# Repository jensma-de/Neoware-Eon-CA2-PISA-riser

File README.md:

# Neoware Eon/CA2 PISA to ISA/PCI Riser Card

An exact 1:1 reproduction of the original riser card used in Neoware Eon/CA2 systems. This riser card enables the conversion of PISA to ISA and PCI.

[./production.zip](./production.zip) contains gerber files and everything needed to manufacture this card.

## Features

- **Function**: Converts PISA to ISA & PCI
- **Voltage Converter**: I added an integrated -5V voltage converter for the ISA slot
- **Condition**: New, 1:1 reproduction of the original card (except for the -5V voltage converter)
- **Compatibility**: Identical to the card installed in Neoware Eon/CA2

# Schematics

I annotated the schematics to clarify some quirks:

## License

This project is licensed under the MIT License. See the [LICENSE](LICENSE) file for more details.

## Thanks

I extend my sincere gratitude to (https://www.parkytowers.me.uk/) for the generous loan of an original Neoware CA2 riser card. Your support was instrumental in enabling the accurate reproduction of this hardware. Thank you for your invaluable assistance.

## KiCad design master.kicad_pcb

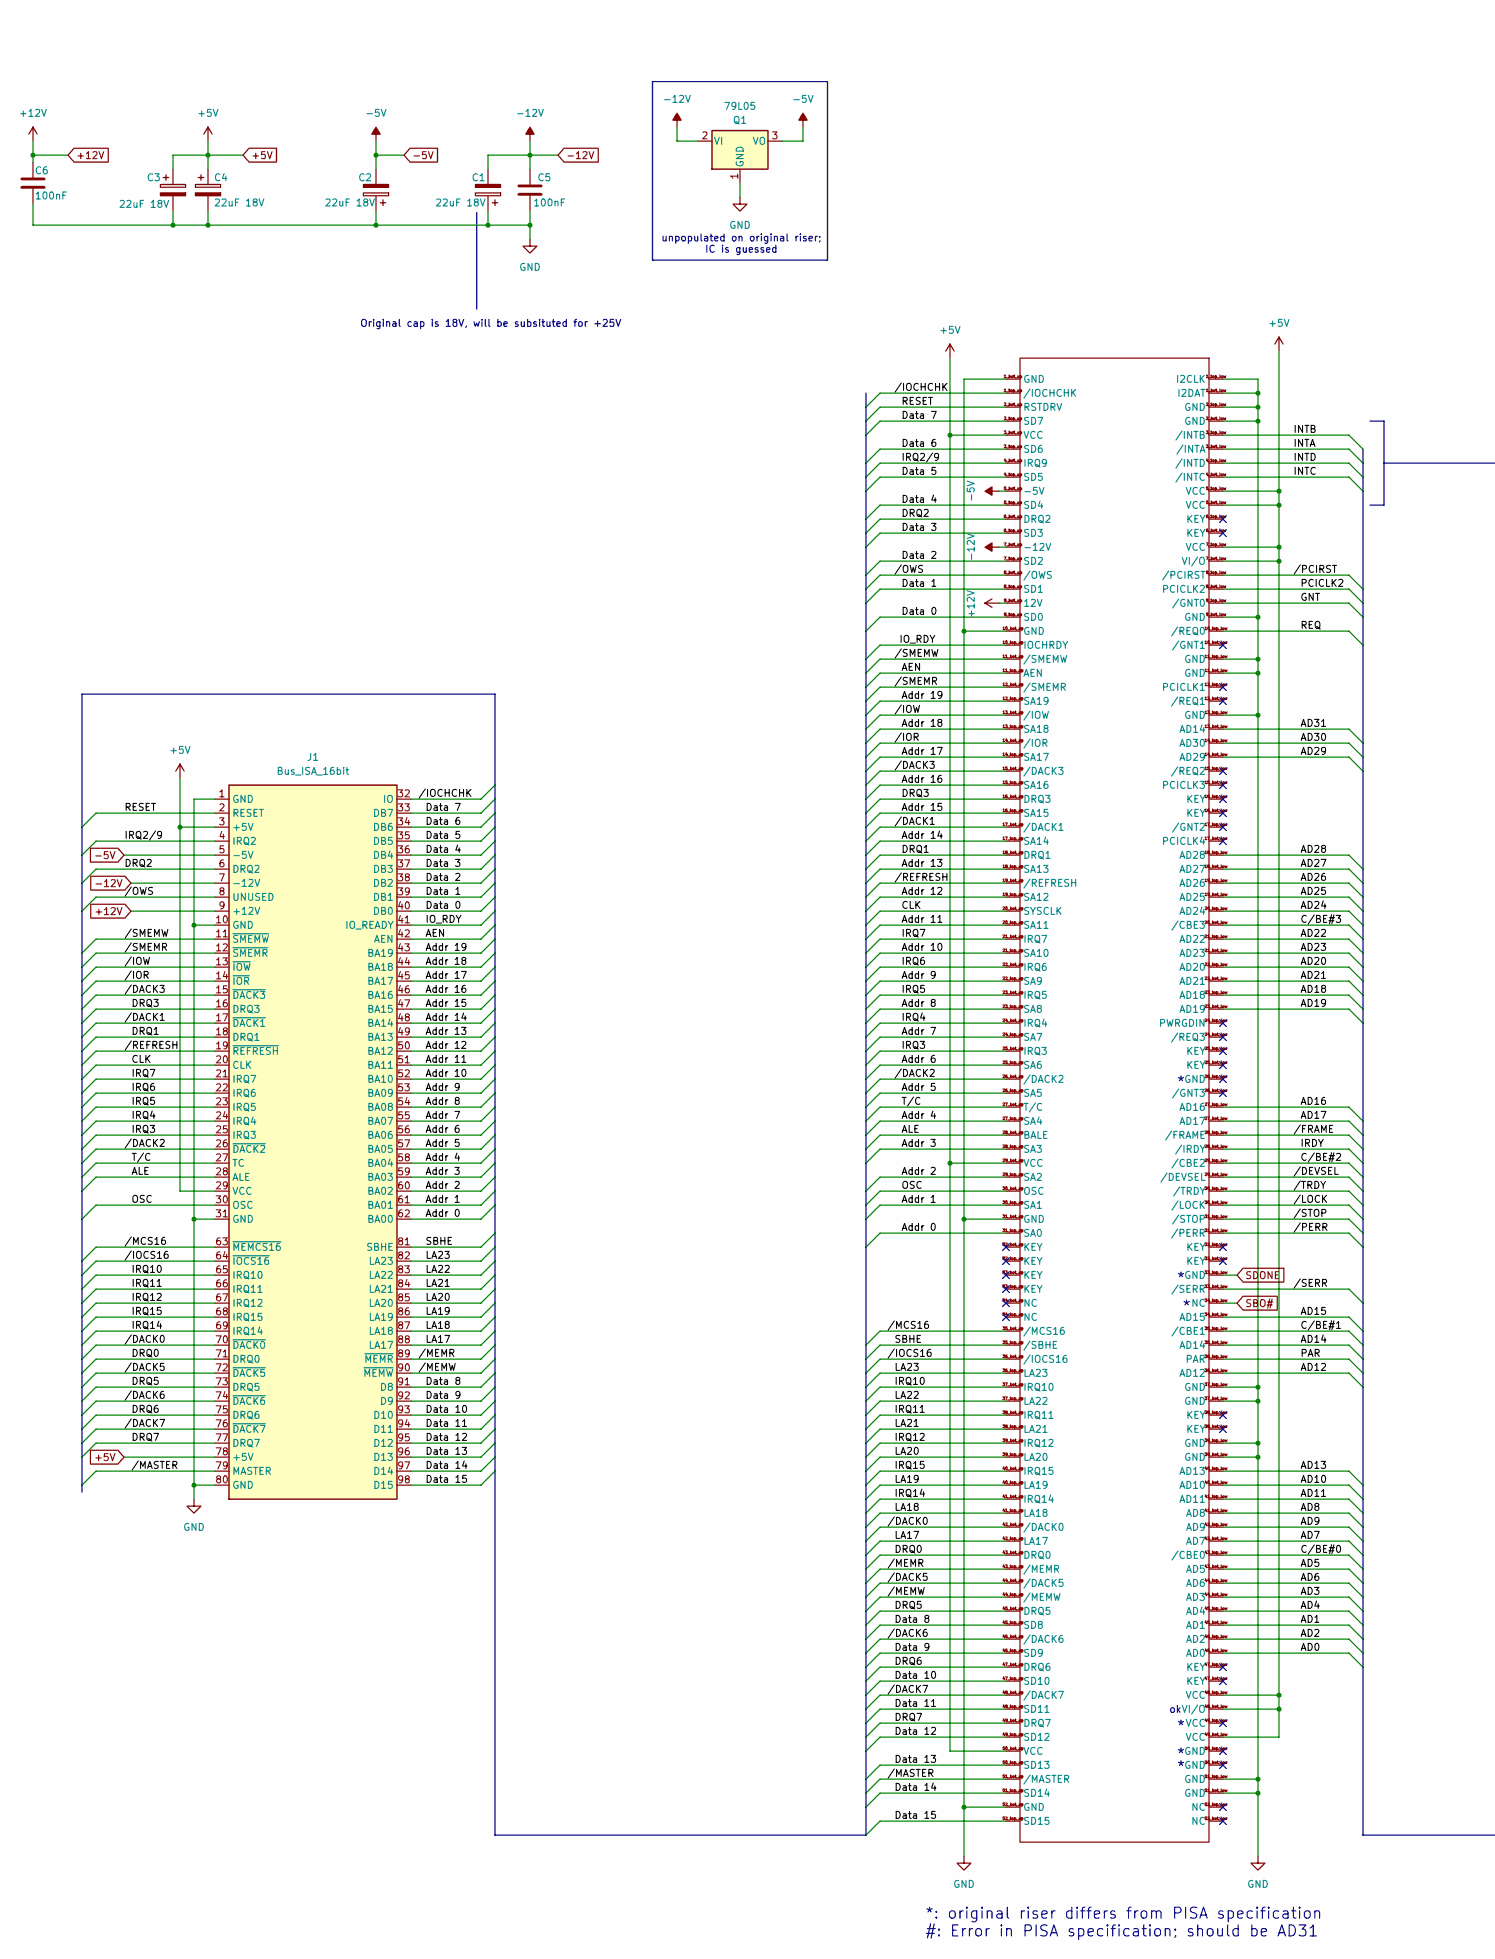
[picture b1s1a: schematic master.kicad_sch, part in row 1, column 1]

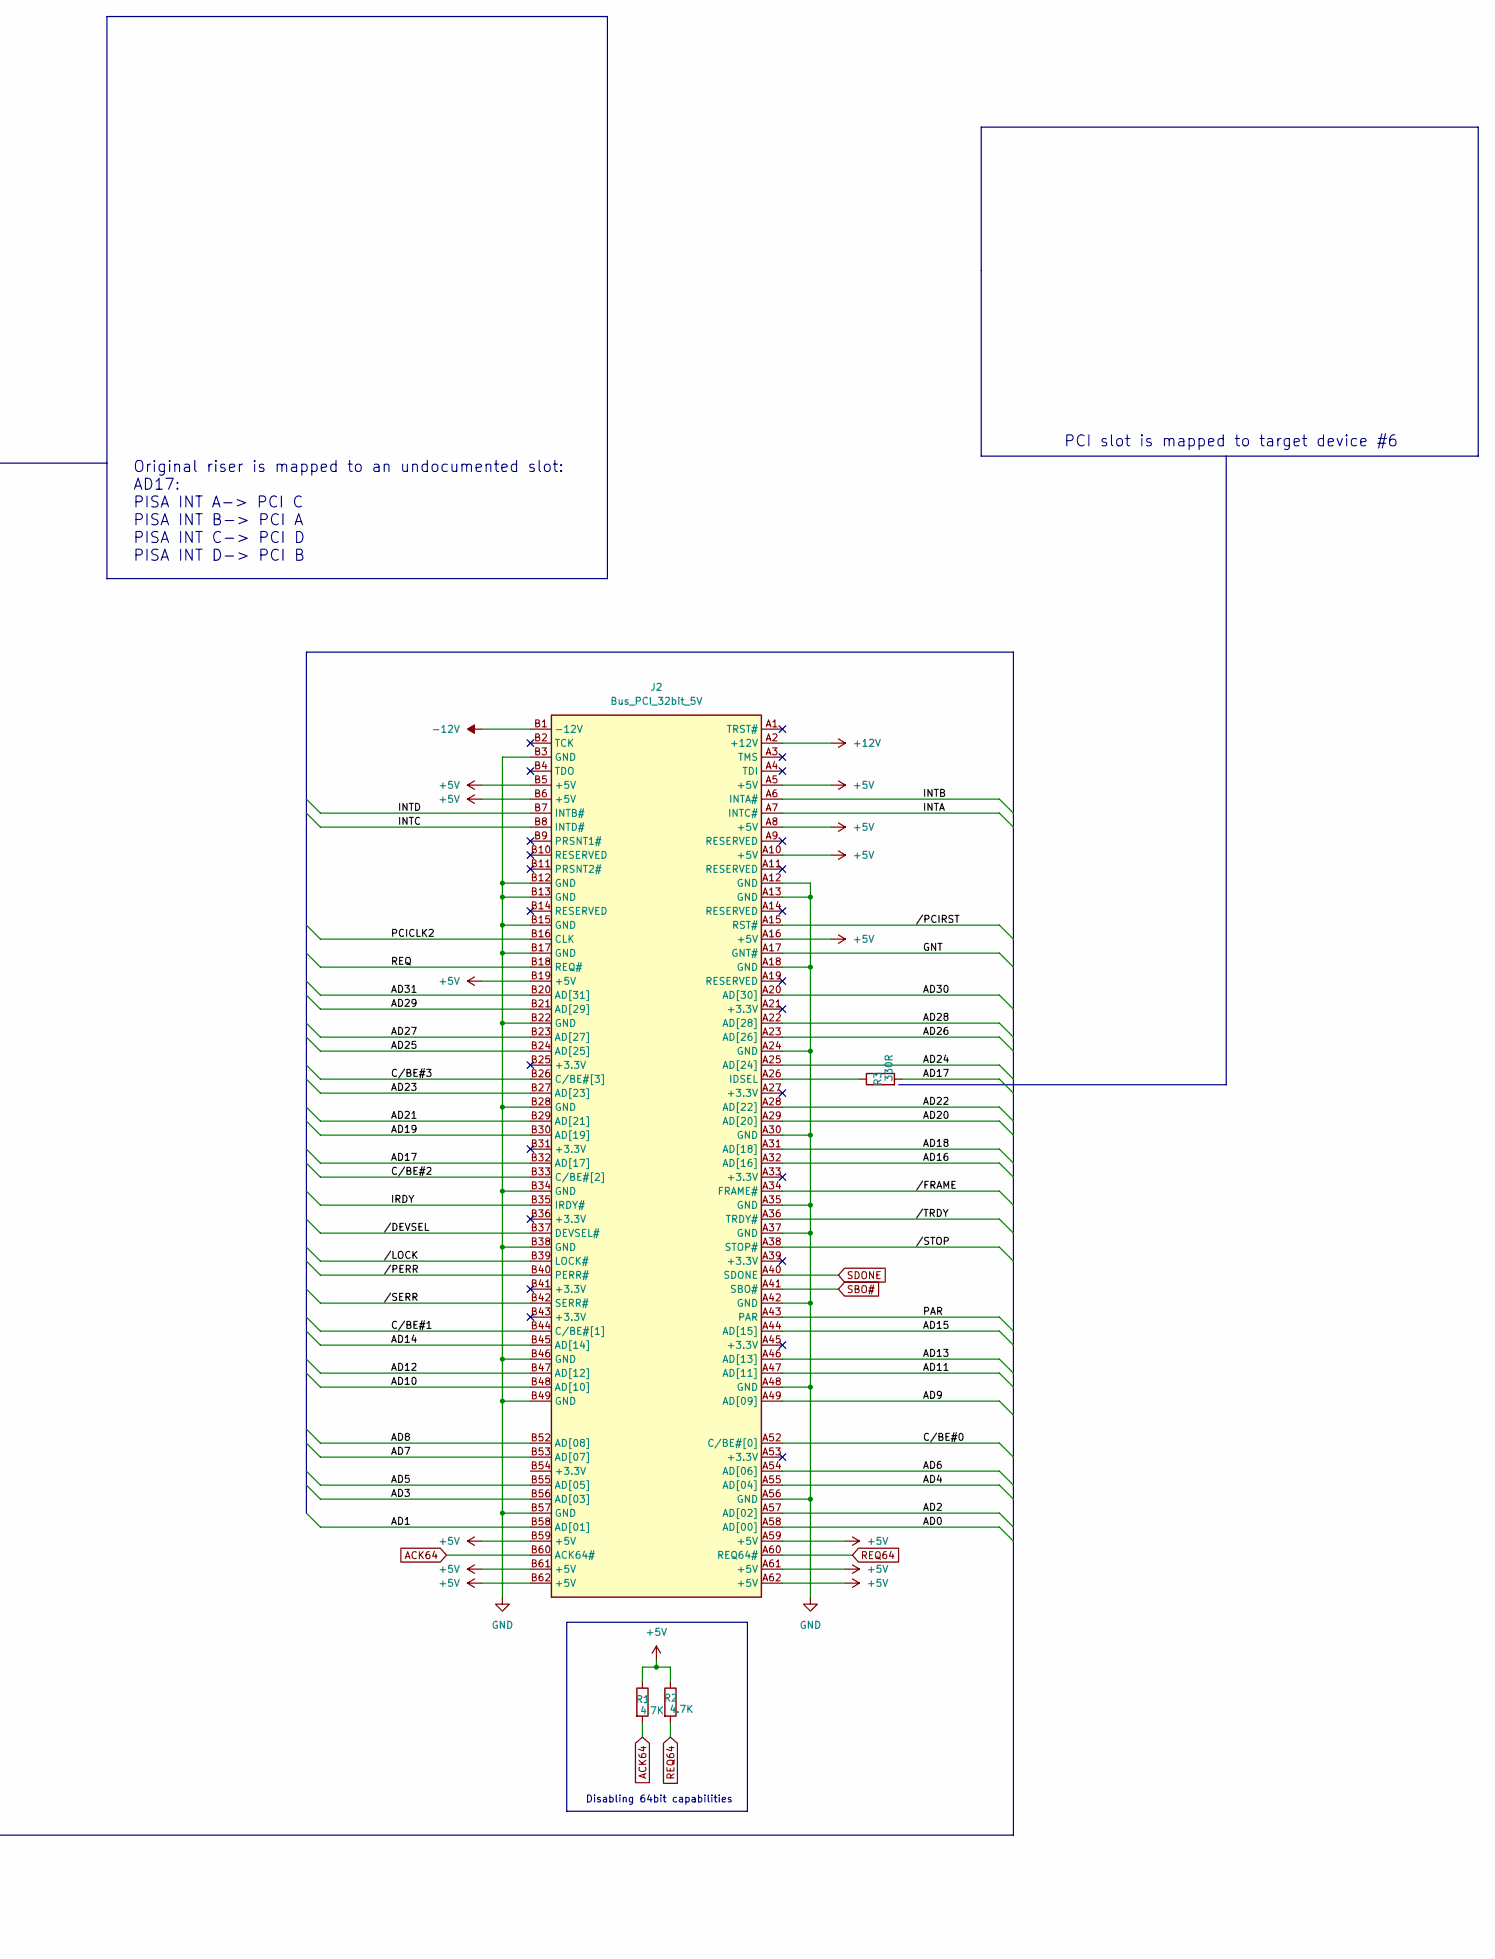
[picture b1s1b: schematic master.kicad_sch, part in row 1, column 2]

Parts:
C1, C2, C3, C4: 22uF 18V; CP_Radial_D5.0mm_P2.00mm
C5, C6: 100nF; C_Disc_D5.0mm_W2.5mm_P5.00mm
J1: Bus_ISA_16bit; ISA 98PIN
J2: Bus_PCI_32bit_5V; PCI
Q1: 79L05; TO-92_Inline_Wide
R1, R2: 4.7K; R_Axial_DIN0207_L6.3mm_D2.5mm_P10.16mm_Horizontal
R3: 330R; R_Axial_DIN0207_L6.3mm_D2.5mm_P10.16mm_Horizontal
U1: EISA

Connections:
+5V: C3.1, C4.1, J1.3 (+5V), J1.29 (VCC), J1.78 (+5V), J2.A5 (+5V), J2.A8 (+5V), J2.A10 (+5V), J2.A16 (+5V), J2.A59 (+5V), J2.A61 (+5V), J2.A62 (+5V), J2.B5 (+5V), J2.B6 (+5V), J2.B19 (+5V), J2.B59 (+5V), J2.B61 (+5V), J2.B62 (+5V), R1.1, R2.1, U1.3_bot_up (VCC), U1.5_bot_low (VCC), U1.5_top_low (VCC), U1.7_bot_low (VI/O), U1.7_top_low (VCC), U1.29_bot_up (VCC), U1.48_bot_low (VI/O), U1.48_top_low (VCC), U1.49_bot_low (VCC), U1.50_bot_up (VCC)
+12V: C6.1, J1.9 (+12V), J2.A2 (+12V), U1.9_bot_up (12V)
-5V: C2.2, J1.5 (-5V), Q1.3 (VO), U1.5_bot_up (-5V)
-12V: C1.2, C5.1, J1.7 (-12V), J2.B1 (-12V), Q1.2 (VI), U1.7_bot_up (-12V)
/AD0: J2.A58 (AD[00]), U1.46_bot_low (AD0)
/AD1: J2.B58 (AD[01]), U1.45_bot_low (AD1)
/AD2: J2.A57 (AD[02]), U1.46_top_low (AD2)
/AD3: J2.B56 (AD[03]), U1.44_bot_low (AD3)
/AD4: J2.A55 (AD[04]), U1.45_top_low (AD4)
/AD5: J2.B55 (AD[05]), U1.43_bot_low (AD5)
/AD6: J2.A54 (AD[06]), U1.44_top_low (AD6)
/AD7: J2.B53 (AD[07]), U1.42_bot_low (AD7)
/AD8: J2.B52 (AD[08]), U1.41_bot_low (AD8)
/AD9: J2.A49 (AD[09]), U1.42_top_low (AD9)
/AD10: J2.B48 (AD[10]), U1.40_bot_low (AD10)
/AD11: J2.A47 (AD[11]), U1.41_top_low (AD11)
/AD12: J2.B47 (AD[12]), U1.36_bot_low (AD12)
/AD13: J2.A46 (AD[13]), U1.40_top_low (AD13)
/AD14: J2.B45 (AD[14]), U1.35_bot_low (AD14)
/AD15: J2.A44 (AD[15]), U1.34_bot_low (AD15)
/AD16: J2.A32 (AD[16]), U1.27_top_low (AD16)
/AD17: J2.B32 (AD[17]), R3.2, U1.27_bot_low (AD17)
/AD18: J2.A31 (AD[18]), U1.23_top_low (AD18)
/AD19: J2.B30 (AD[19]), U1.23_bot_low (AD19)
/AD20: J2.A29 (AD[20]), U1.22_top_low (AD20)
/AD21: J2.B29 (AD[21]), U1.22_bot_low (AD21)
/AD22: J2.A28 (AD[22]), U1.21_top_low (AD22)
/AD23: J2.B27 (AD[23]), U1.21_bot_low (AD23)
/AD24: J2.A25 (AD[24]), U1.20_top_low (AD24)
/AD25: J2.B24 (AD[25]), U1.19_bot_low (AD25)
/AD26: J2.A23 (AD[26]), U1.19_top_low (AD26)
/AD27: J2.B23 (AD[27]), U1.18_bot_low (AD27)
/AD28: J2.A22 (AD[28]), U1.18_top_low (AD28)
/AD29: J2.B21 (AD[29]), U1.14_bot_low (AD29)
/AD30: J2.A20 (AD[30]), U1.14_top_low (AD30)
/AD31: J2.B20 (AD[31]), U1.13_bot_low (AD14)
/AEN: J1.42 (AEN), U1.11_top_up (AEN)
/ALE: J1.28 (ALE), U1.28_bot_up (BALE)
/Addr 0: J1.62 (BA00), U1.31_top_up (SA0)
/Addr 1: J1.61 (BA01), U1.30_top_up (SA1)
/Addr 2: J1.60 (BA02), U1.29_top_up (SA2)
/Addr 3: J1.59 (BA03), U1.28_top_up (SA3)
/Addr 4: J1.58 (BA04), U1.27_top_up (SA4)
/Addr 5: J1.57 (BA05), U1.26_top_up (SA5)
/Addr 6: J1.56 (BA06), U1.25_top_up (SA6)
/Addr 7: J1.55 (BA07), U1.24_top_up (SA7)
/Addr 8: J1.54 (BA08), U1.23_top_up (SA8)
/Addr 9: J1.53 (BA09), U1.22_top_up (SA9)
/Addr 10: J1.52 (BA10), U1.21_top_up (SA10)
/Addr 11: J1.51 (BA11), U1.20_top_up (SA11)
/Addr 12: J1.50 (BA12), U1.19_top_up (SA12)
/Addr 13: J1.49 (BA13), U1.18_top_up (SA13)
/Addr 14: J1.48 (BA14), U1.17_top_up (SA14)
/Addr 15: J1.47 (BA15), U1.16_top_up (SA15)
/Addr 16: J1.46 (BA16), U1.15_top_up (SA16)
/Addr 17: J1.45 (BA17), U1.14_top_up (SA17)
/Addr 18: J1.44 (BA18), U1.13_top_up (SA18)
/Addr 19: J1.43 (BA19), U1.12_top_up (SA19)
/CLK: J1.20 (CLK), U1.20_bot_up (SYSCLK)
/C/BE#0: J2.A52 (C/BE#[0]), U1.43_top_low (/CBE0)
/C/BE#1: J2.B44 (C/BE#[1]), U1.35_top_low (/CBE1)
/C/BE#2: J2.B33 (C/BE#[2]), U1.29_top_low (/CBE2)
/C/BE#3: J2.B26 (C/BE#[3]), U1.20_bot_low (/CBE3)
/DRQ0: J1.71 (DRQ0), U1.43_bot_up (DRQ0)
/DRQ1: J1.18 (DRQ1), U1.18_bot_up (DRQ1)
/DRQ2: J1.6 (DRQ2), U1.6_bot_up (DRQ2)
/DRQ3: J1.16 (DRQ3), U1.16_bot_up (DRQ3)
/DRQ5: J1.73 (DRQ5), U1.45_bot_up (DRQ5)
/DRQ6: J1.75 (DRQ6), U1.47_bot_up (DRQ6)
/DRQ7: J1.77 (DRQ7), U1.49_bot_up (DRQ7)
/Data 0: J1.40 (DB0), U1.9_top_up (SD0)
/Data 1: J1.39 (DB1), U1.8_top_up (SD1)
/Data 2: J1.38 (DB2), U1.7_top_up (SD2)
/Data 3: J1.37 (DB3), U1.6_top_up (SD3)
/Data 4: J1.36 (DB4), U1.5_top_up (SD4)
/Data 5: J1.35 (DB5), U1.4_top_up (SD5)
/Data 6: J1.34 (DB6), U1.3_top_up (SD6)
/Data 7: J1.33 (DB7), U1.2_top_up (SD7)
/Data 8: J1.91 (D8), U1.45_top_up (SD8)
/Data 9: J1.92 (D9), U1.46_top_up (SD9)
/Data 10: J1.93 (D10), U1.47_top_up (SD10)
/Data 11: J1.94 (D11), U1.48_top_up (SD11)
/Data 12: J1.95 (D12), U1.49_top_up (SD12)
/Data 13: J1.96 (D13), U1.50_top_up (SD13)
/Data 14: J1.97 (D14), U1.51_top_up (SD14)
/Data 15: J1.98 (D15), U1.52_top_up (SD15)
/GNT: J2.A17 (GNT#), U1.9_top_low (/GNT0)
/INTA: J2.A7 (INTC#), U1.3_bot_low (/INTA)
/INTB: J2.A6 (INTA#), U1.3_top_low (/INTB)
/INTC: J2.B8 (INTD#), U1.4_bot_low (/INTC)
/INTD: J2.B7 (INTB#), U1.4_top_low (/INTD)
/IO_RDY: J1.41 (IO_READY), U1.10_top_up (IOCHRDY)
/IRDY: J2.B35 (IRDY#), U1.28_bot_low (/IRDY)
/IRQ2/9: J1.4 (IRQ2), U1.4_bot_up (IRQ9)
/IRQ3: J1.25 (IRQ3), U1.25_bot_up (IRQ3)
/IRQ4: J1.24 (IRQ4), U1.24_bot_up (IRQ4)
/IRQ5: J1.23 (IRQ5), U1.23_bot_up (IRQ5)
/IRQ6: J1.22 (IRQ6), U1.22_bot_up (IRQ6)
/IRQ7: J1.21 (IRQ7), U1.21_bot_up (IRQ7)
/IRQ10: J1.65 (IRQ10), U1.37_bot_up (IRQ10)
/IRQ11: J1.66 (IRQ11), U1.38_bot_up (IRQ11)
/IRQ12: J1.67 (IRQ12), U1.39_bot_up (IRQ12)
/IRQ14: J1.69 (IRQ14), U1.41_bot_up (IRQ14)
/IRQ15: J1.68 (IRQ15), U1.40_bot_up (IRQ15)
/LA17: J1.88 (LA17), U1.42_top_up (LA17)
/LA18: J1.87 (LA18), U1.41_top_up (LA18)
/LA19: J1.86 (LA19), U1.40_top_up (LA19)
/LA20: J1.85 (LA20), U1.39_top_up (LA20)
/LA21: J1.84 (LA21), U1.38_top_up (LA21)
/LA22: J1.83 (LA22), U1.37_top_up (LA22)
/LA23: J1.82 (LA23), U1.36_top_up (LA23)
/OSC: J1.30 (OSC), U1.30_bot_up (OSC)
/PAR: J2.A43 (PAR), U1.36_top_low (PAR)
/PCICLK2: J2.B16 (CLK), U1.8_bot_low (PCICLK2)
/REQ: J2.B18 (REQ#), U1.10_top_low (/REQ0)
/RESET: J1.2 (RESET), U1.2_bot_up (RSTDRV)
/SBHE: J1.81 (SBHE), U1.35_top_up (/SBHE)
/T/C: J1.27 (TC), U1.27_bot_up (T/C)
//DACK0: J1.70 (~DACK0), U1.42_bot_up (/DACK0)
//DACK1: J1.17 (~DACK1), U1.17_bot_up (/DACK1)
//DACK2: J1.26 (~DACK2), U1.26_bot_up (/DACK2)
//DACK3: J1.15 (~DACK3), U1.15_bot_up (/DACK3)
//DACK5: J1.72 (~DACK5), U1.44_bot_up (/DACK5)
//DACK6: J1.74 (~DACK6), U1.46_bot_up (/DACK6)
//DACK7: J1.76 (~DACK7), U1.48_bot_up (/DACK7)
//DEVSEL: J2.B37 (DEVSEL#), U1.29_bot_low (/DEVSEL)
//FRAME: J2.A34 (FRAME#), U1.28_top_low (/FRAME)
//IOCHCHK: J1.32 (IO), U1.1_top_up (/IOCHCHK)
//IOCS16: J1.64 (~IOCS16), U1.36_bot_up (/IOCS16)
//IOR: J1.14 (~IOR), U1.14_bot_up (/IOR)
//IOW: J1.13 (~IOW), U1.13_bot_up (/IOW)
//LOCK: J2.B39 (LOCK#), U1.30_bot_low (/LOCK)
//MASTER: J1.79 (MASTER), U1.51_bot_up (/MASTER)
//MCS16: J1.63 (~MEMCS16), U1.35_bot_up (/MCS16)
//MEMR: J1.89 (~MEMR), U1.43_top_up (/MEMR)
//MEMW: J1.90 (~MEMW), U1.44_top_up (/MEMW)
//OWS: J1.8 (UNUSED), U1.8_bot_up (/OWS)
//PCIRST: J2.A15 (RST#), U1.8_top_low (/PCIRST)
//PERR: J2.B40 (PERR#), U1.31_bot_low (/PERR)
//REFRESH: J1.19 (~REFRESH), U1.19_bot_up (/REFRESH)
//SERR: J2.B42 (SERR#), U1.33_bot_low (/SERR)
//SMEMR: J1.12 (~SMEMR), U1.12_bot_up (/SMEMR)
//SMEMW: J1.11 (~SMEMW), U1.11_bot_up (/SMEMW)
//STOP: J2.A38 (STOP#), U1.31_top_low (/STOP)
//TRDY: J2.A36 (TRDY#), U1.30_top_low (/TRDY)
ACK64: J2.B60 (ACK64#), R1.2
GND: C1.1, C2.1, C3.2, C4.2, C5.2, C6.2, J1.1 (GND), J1.10 (GND), J1.31 (GND), J1.80 (GND), J2.A12 (GND), J2.A13 (GND), J2.A18 (GND), J2.A24 (GND), J2.A30 (GND), J2.A35 (GND), J2.A37 (GND), J2.A42 (GND), J2.A48 (GND), J2.A56 (GND), J2.B3 (GND), J2.B12 (GND), J2.B13 (GND), J2.B15 (GND), J2.B17 (GND), J2.B22 (GND), J2.B28 (GND), J2.B34 (GND), J2.B38 (GND), J2.B46 (GND), J2.B49 (GND), J2.B57 (GND), Q1.1 (GND), U1.1_bot_low (I2DAT), U1.1_bot_up (GND), U1.1_top_low (I2CLK), U1.2_bot_low (GND), U1.2_top_low (GND), U1.9_bot_low (GND), U1.10_bot_up (GND), U1.11_bot_low (GND), U1.11_top_low (GND), U1.13_top_low (GND), U1.31_bot_up (GND), U1.37_bot_low (GND), U1.37_top_low (GND), U1.39_bot_low (GND), U1.39_top_low (GND), U1.51_bot_low (GND), U1.51_top_low (GND), U1.52_bot_up (GND)
unnamed: J2.A26 (IDSEL), R3.1
REQ64: J2.A60 (REQ64#), R2.2
SBO#: J2.A41 (SBO#), U1.34_top_low (NC)
SDONE: J2.A40 (SDONE), U1.33_top_low (GND)

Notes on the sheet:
PCI slot is mapped to target device #6
Original riser is mapped to an undocumented slot: AD17: PISA INT A-> PCI C PISA INT B-> PCI A PISA INT C-> PCI D PISA INT D-> PCI B
unpopulated on original riser; IC is guessed
Disabling 64bit capabilities
*: original riser differs from PISA specification #: Error in PISA specification; should be AD31
Original cap is 18V, will be subsituted for +25V

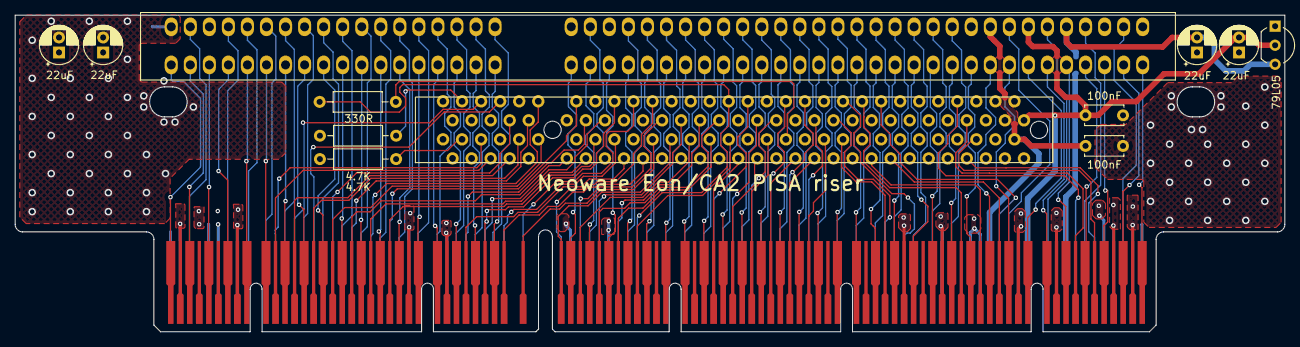
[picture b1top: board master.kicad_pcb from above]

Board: 4 copper layers, 169.3 x 42.2 mm, 13 parts (0 on the bottom side), 151 nets.

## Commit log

2024-10-12 init
    init
2024-10-12 Create README.md
    Thanks and minor changes
2024-10-12 Update README.md
    minor changes
